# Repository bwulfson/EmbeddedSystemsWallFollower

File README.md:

# Wall Follower Robot
This repo contains files and information regarding the robot designed for Embedded Systems class. 
- solidModels: Contains STEP and STL files for 3d printing. 
- software: Contains Tiva C firmware, bootloaders, and some bash scripts (potentially)
- electrical: Contains overall electrical schematic and connections, and later PCB daughterboard designs/schematics

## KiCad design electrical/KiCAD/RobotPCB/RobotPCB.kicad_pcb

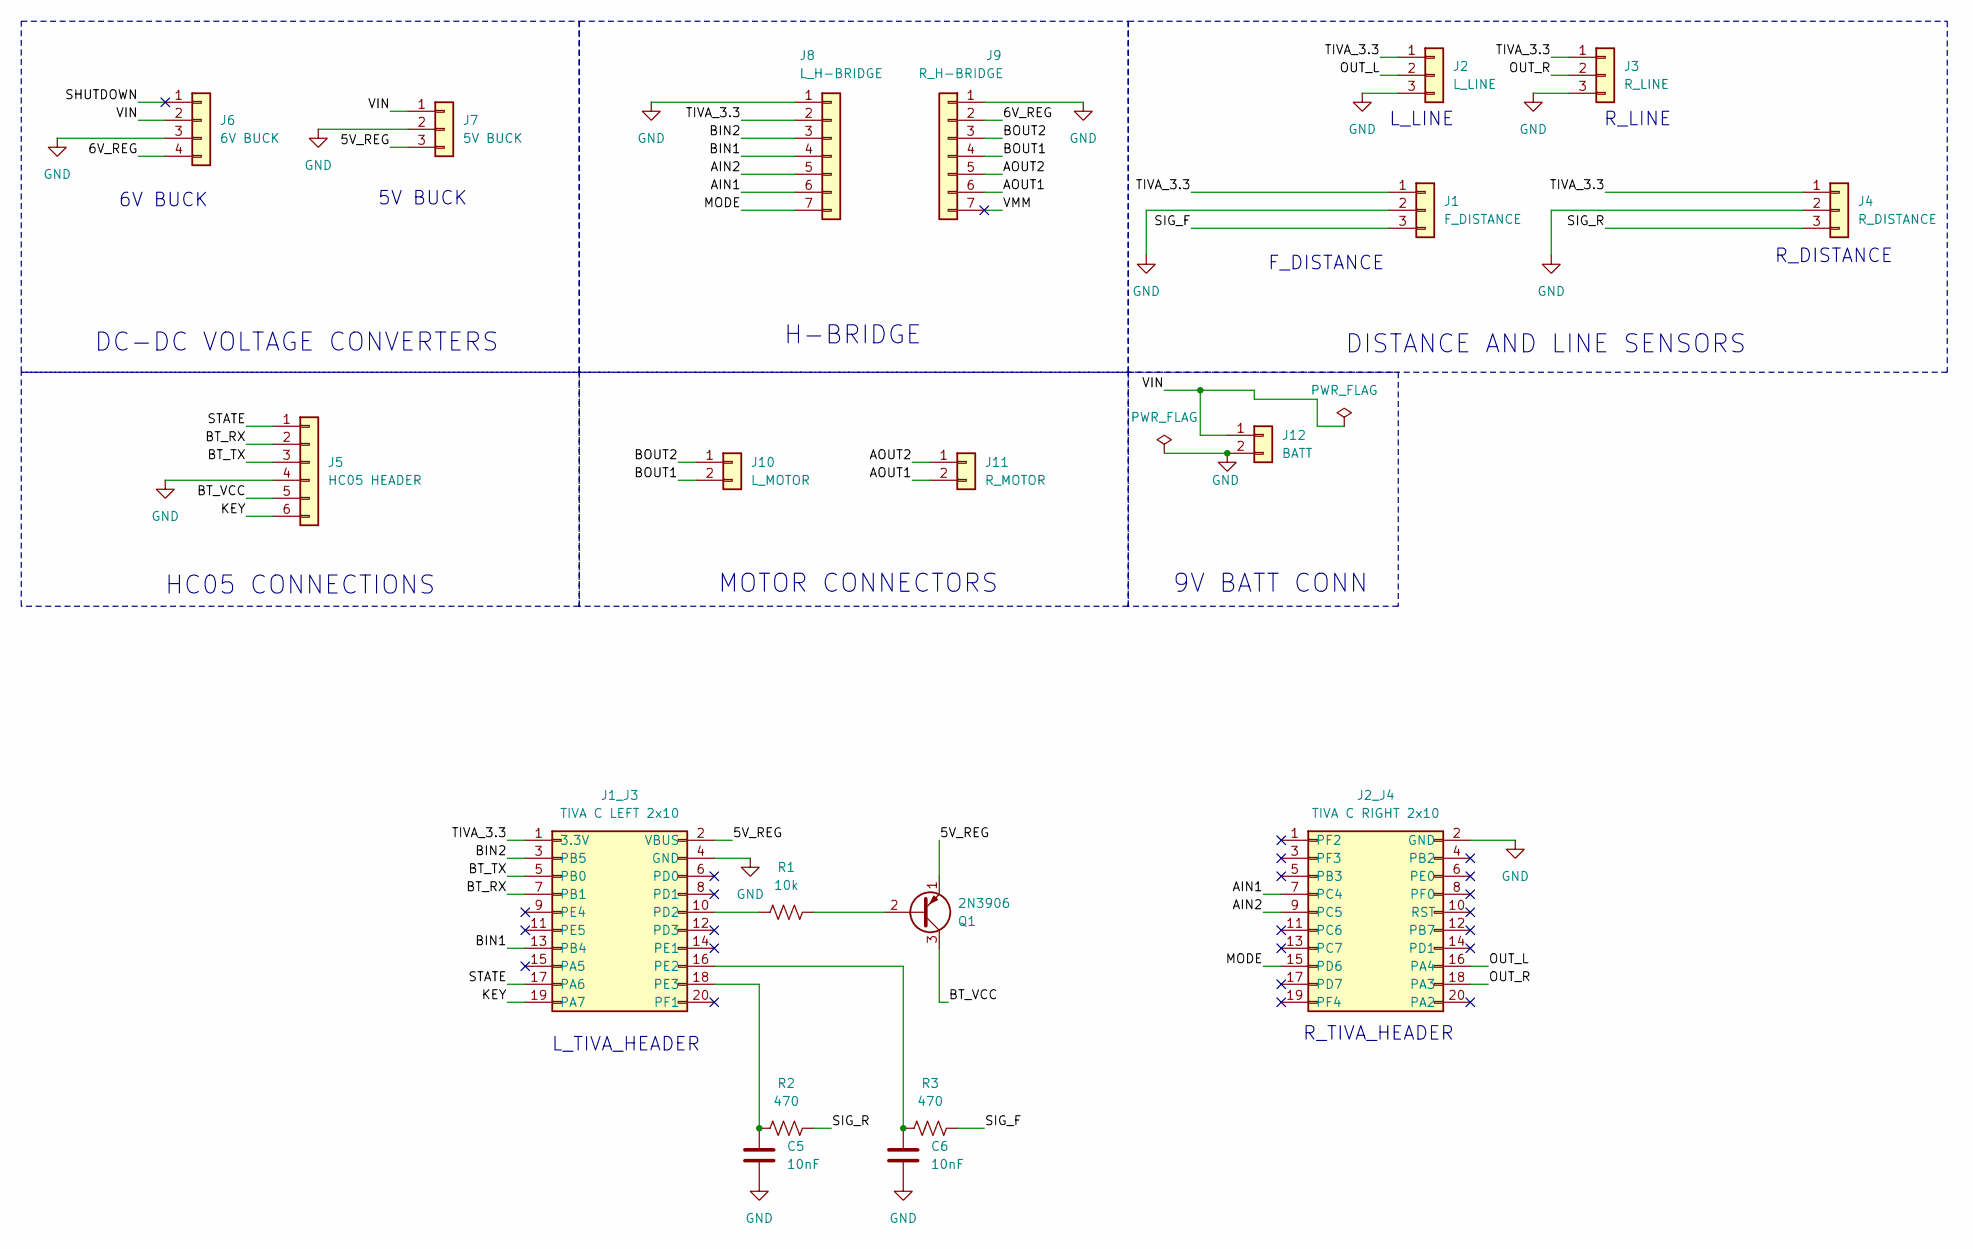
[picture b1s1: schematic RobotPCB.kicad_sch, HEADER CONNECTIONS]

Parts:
C5, C6: 10nF; C_0805_2012Metric_Pad1.18x1.45mm_HandSolder
J1: F_DISTANCE; PinHeader_1x03_P2.54mm_Vertical
J1_J3: TIVA C LEFT 2x10; PinHeader_2x10_P2.54mm_Vertical
J2: L_LINE; PinHeader_1x03_P2.54mm_Vertical
J2_J4: TIVA C RIGHT 2x10; PinHeader_2x10_P2.54mm_Vertical
J3: R_LINE; PinHeader_1x03_P2.54mm_Vertical
J4: R_DISTANCE; PinHeader_1x03_P2.54mm_Vertical
J5: HC05 HEADER; PinHeader_1x06_P2.54mm_Vertical
J6: 6V BUCK; PinHeader_1x04_P2.54mm_Vertical
J7: 5V BUCK; PinHeader_1x03_P2.54mm_Vertical
J8: L_H-BRIDGE; PinHeader_1x07_P2.54mm_Vertical
J9: R_H-BRIDGE; PinHeader_1x07_P2.54mm_Vertical
J10: L_MOTOR; PinHeader_1x02_P2.54mm_Vertical
J11: R_MOTOR; PinHeader_1x02_P2.54mm_Vertical
J12: BATT; PinHeader_1x02_P2.54mm_Vertical
Q1: 2N3906; TO-92_Inline
R1: 10k; R_0805_2012Metric_Pad1.20x1.40mm_HandSolder
R2, R3: 470; R_0805_2012Metric_Pad1.20x1.40mm_HandSolder

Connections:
/RobotPCB/5V_REG: J1_J3.2 (VBUS), J7.3, Q1.1 (E)
/RobotPCB/6V_REG: J6.4, J9.2
/RobotPCB/AIN1: J2_J4.7 (PC4), J8.6
/RobotPCB/AIN2: J2_J4.9 (PC5), J8.5
/RobotPCB/AOUT1: J9.6, J11.2
/RobotPCB/AOUT2: J9.5, J11.1
/RobotPCB/BIN1: J1_J3.13 (PB4), J8.4
/RobotPCB/BIN2: J1_J3.3 (PB5), J8.3
/RobotPCB/BOUT1: J9.4, J10.2
/RobotPCB/BOUT2: J9.3, J10.1
/RobotPCB/BT_RX: J1_J3.7 (PB1), J5.2
/RobotPCB/BT_TX: J1_J3.5 (PB0), J5.3
/RobotPCB/BT_VCC: J5.5, Q1.3 (C)
/RobotPCB/KEY: J1_J3.19 (PA7), J5.6
/RobotPCB/MODE: J2_J4.15 (PD6), J8.7
/RobotPCB/OUT_L: J2.2, J2_J4.16 (PA4)
/RobotPCB/OUT_R: J2_J4.18 (PA3), J3.2
/RobotPCB/SHUTDOWN: J6.1
/RobotPCB/SIG_F: J1.3, R3.2
/RobotPCB/SIG_R: J4.3, R2.2
/RobotPCB/STATE: J1_J3.17 (PA6), J5.1
/RobotPCB/TIVA_3.3: J1.1, J1_J3.1 (3.3V), J2.1, J3.1, J4.1, J8.2
/RobotPCB/VIN: J6.2, J7.1, J12.1
/RobotPCB/VMM: J9.7
GND: C5.2, C6.2, J1.2, J1_J3.4 (GND), J2.3, J2_J4.2 (GND), J3.3, J4.2, J5.4, J6.3, J7.2, J8.1, J9.1, J12.2
unnamed: J1_J3.10 (PD2), R1.1
unnamed: C6.1, J1_J3.16 (PE2), R3.1
unnamed: C5.1, J1_J3.18 (PE3), R2.1
unnamed: Q1.2 (B), R1.2

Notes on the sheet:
F_DISTANCE
R_DISTANCE
L_TIVA_HEADER
H-BRIDGE
5V BUCK
R_TIVA_HEADER
DC-DC VOLTAGE CONVERTERS
DISTANCE AND LINE SENSORS
L_LINE
6V BUCK
MOTOR CONNECTORS
R_LINE
HC05 CONNECTIONS
9V BATT CONN

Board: 2 copper layers, 20 parts (0 on the bottom side), 27 nets, no tracks yet.
